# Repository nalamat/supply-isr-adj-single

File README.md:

# supply-isr-adj-single
Integrated switching adjustable single power supply based on TI TPS54232

## Application notes
Input voltage range: 3.5 to 28v  
Output voltage range: 0.8 to 25v in steps of 0.1v  
Maximum output current: 2A  
Normally off, turns on by shorting EN pin header to On  
Output is also adjustable using shorting jumpers on Vadj pin header  
Output voltage is calculated by sum of all shorted headers plus 0.8v  
LED is an indicator of input power supply, not output

## License
Licensed under GPLv3  
Copyright 2016 NESH@NJIT

Neural Engineering of Speech and Hearing  
New Jersey Institute of Technology  
http://centers.njit.edu/nesh

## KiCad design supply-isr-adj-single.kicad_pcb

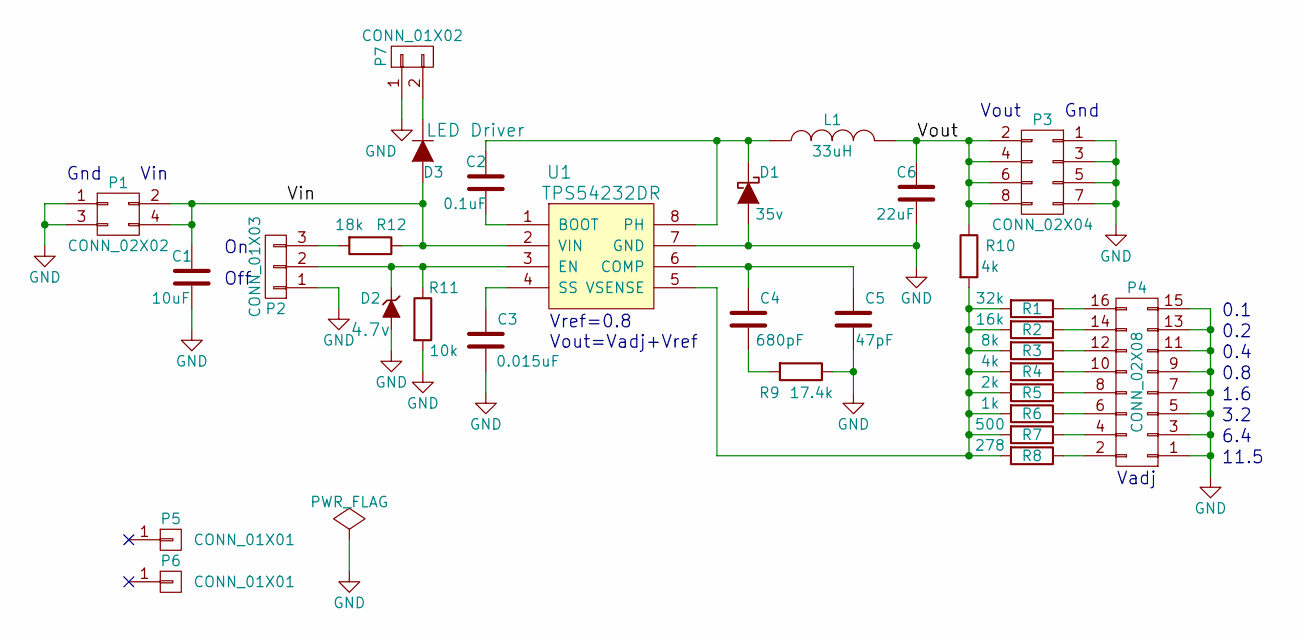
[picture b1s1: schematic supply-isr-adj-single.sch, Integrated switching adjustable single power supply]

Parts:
C1: GRM319R6YA106KA12D; C_1206
C2: GRM188R71E104KA01D; C_0603
C3: GRM155R71H153KA12J; C_0402
C4: CL05B681KB5NNNC; C_0402
C5: C0805C470KCRACTU; C_0805
C6: GRM31CR61E226KE15L; C_1206
D1: DB2W40200L; SOD-123
D2: DZ2J047M0L; SOD-323
D3: NSI45015WT1G; SOD-123
L1: SRP1038A-330M; SRP1038A
P1: CONN_02X02; Pin_Header_Straight_2x02
P2: CONN_01X03; Pin_Header_Straight_1x03
P3: CONN_02X04; Pin_Header_Straight_2x04
P4: CONN_02X08; Pin_Header_Straight_2x08
P5, P6: CONN_01X01; 1pin
P7: CONN_01X02; Pin_Header_Straight_1x02
R1: RC0402FR-0731K6L; R_0402
R2: RC0402FR-0716K2L; R_0402
R3: RC0805FR-078K06L; R_0805
R4, R10: RC0603FR-074K02L; R_0603
R5: RC0805FR-072KL; R_0805
R6: RC0402JR-071KL; R_0402
R7: ERJ-2RKF4990X; R_0402
R8: RC0402FR-07280RL; R_0402
R9: RC0402FR-0717K4L; R_0402
R11: RC0402JR-0710KL; R_0402
R12: RC0603FR-0717K8L; R_0603
U1: TPS54232DR; SOIC-8-N

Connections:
/Vin: C1.1, D3.2 (A), P1.2, P1.4, R12.1, U1.2 (VIN)
/Vout: C6.1, L1.2, P3.2, P3.4, P3.6, P3.8, R10.1
GND: C1.2, C3.2, C5.2, C6.2, D1.2 (A), D2.2 (A), P1.1, P1.3, P2.1, P3.1, P3.3, P3.5, P3.7, P4.1, P4.3, P4.5, P4.7, P4.9, P4.11, P4.13, P4.15, P7.1, R9.1, R11.2, U1.7 (GND)
unnamed: C2.1, D1.1 (K), L1.1, U1.8 (PH)
unnamed: C2.2, U1.1 (BOOT)
unnamed: C3.1, U1.4 (SS)
unnamed: C4.1, C5.1, U1.6 (COMP)
unnamed: C4.2, R9.2
unnamed: D2.1 (K), P2.2, R11.1, U1.3 (EN)
unnamed: D3.1 (K), P7.2
unnamed: P2.3, R12.2
unnamed: P4.2, R8.1
unnamed: P4.4, R7.1
unnamed: P4.6, R6.1
unnamed: P4.8, R5.1
unnamed: P4.10, R4.1
unnamed: P4.12, R3.1
unnamed: P4.14, R2.1
unnamed: P4.16, R1.1
unnamed: R1.2, R2.2, R3.2, R4.2, R5.2, R6.2, R7.2, R8.2, R10.2, U1.5 (VSENSE)

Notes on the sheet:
Vin
Gnd
Off
Vout
0.1
0.2
0.4
0.8
1.6
3.2
6.4
11.5
Vadj
Vref=0.8 Vout=Vadj+Vref

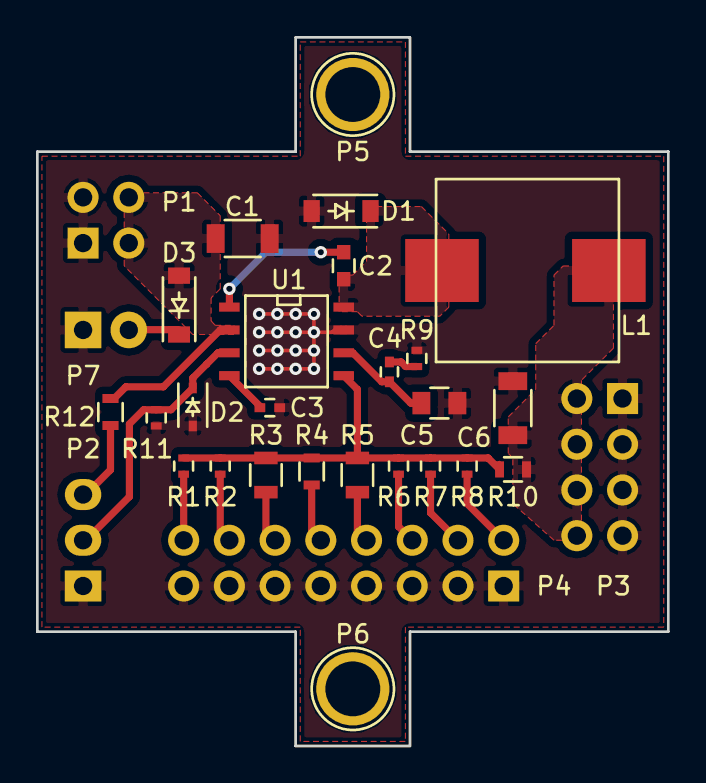
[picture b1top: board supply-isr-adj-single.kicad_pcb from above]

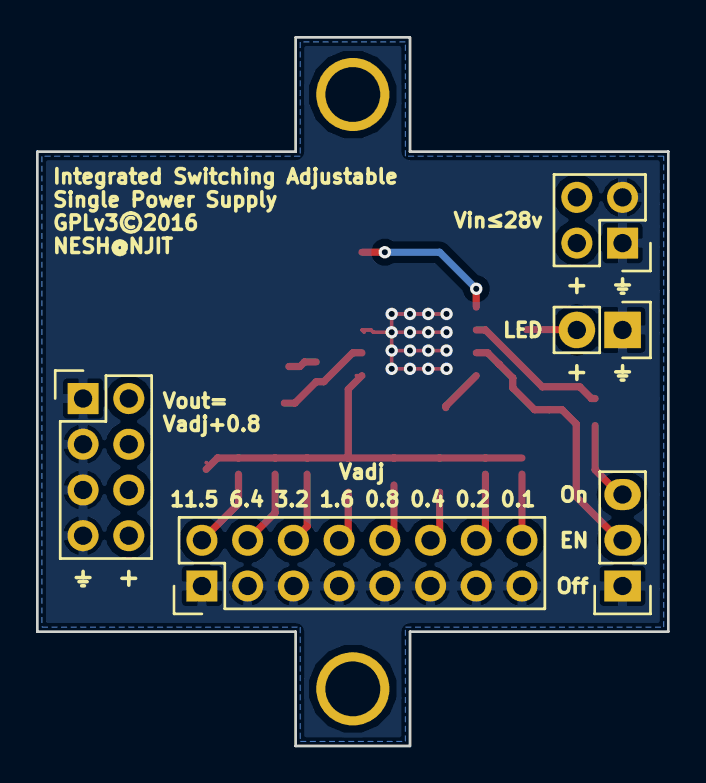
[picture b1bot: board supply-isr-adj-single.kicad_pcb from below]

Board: 2 copper layers, 35.1 x 39.4 mm, 30 parts (5 on the bottom side), 20 nets.

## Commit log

2016-06-20 Add files
2016-06-20 Add readme
2016-06-20 Add .gitignore
2016-06-21 Add license
2016-06-21 Clean up
2016-06-21 Add schematic PDF
2016-06-24 Create footprint for SMD inductor
2016-06-24 Finalize schematic
2016-06-24 Finalize PCB
2016-06-24 Add gerber plots
2016-06-29 Update schematic PDF
2016-07-29 Limit EN pin voltage Add LED port
2016-08-14 Add application notes
2016-08-14 Add new lines

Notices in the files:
supply-isr-adj-single.kicad_pcb:
GPLv3©2016
